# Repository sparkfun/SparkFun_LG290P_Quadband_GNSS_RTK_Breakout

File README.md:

SparkFun Quadband GNSS RTK Breakout - LG290P (Qwiic)
========================================

[*SparkFun Quadband GNSS RTK Breakout - LG290P (Qwiic) (GPS-26620)*](https://www.sparkfun.com/sparkfun-quadband-gnss-rtk-breakout-lg290p-qwiic.html)

The [SparkFun Quadband GNSS RTK Breakout - LG290P (Qwiic)](https://www.sparkfun.com/sparkfun-quadband-gnss-rtk-breakout-lg290p-qwiic.html) features the Quectel LG290P GNSS module. The board's dimensions, pin layout, and connectors are exactly the same as our very popular [SparkFun GPS-RTK-SMA Breakout - ZED-F9P (Qwiic)](https://www.sparkfun.com/sparkfun-gps-rtk-sma-breakout-zed-f9p-qwiic.html); and can be used as a drop-in replacement. The board also accommodates users with a diverse choice of interfaces including UART, SPI*, and I2C*.

The LG290P module is a quad-band, multi-constellation, high-precision, RTK GNSS receiver. The module is capable of simultaneously receiving signals from the `L1`, `L2`, `L5`, and `L6`/`E6` frequency bands of the GPS, GLONASS, Galileo, BDS, QZSS, and NavIC GNSS constellations. In addition, the module supports SBAS augmentation systems (WASS, EGNOS, BDSBAS, MSAS, GAGAN, and SDCM), PPP services* (BDS PPP-B2b, QZSS CLAS, MADOCA-PPP, and Galileo HAS), and RTK corrections for precision navigation with a fast convergence time and reliable performance.

The built-in NIC anti-jamming unit provides professional-grade interference signal detection and elimination algorithms, which effectively mitigate against multiple narrow-band interference sources and significantly improves the signal reception performance in complex electromagnetic environments. Additionally, the embedded algorithms ensure reliable positioning in complex scenarios such as urban environments and deep tree cover.

With its performance advantages of high-precision and low power consumption, this board is an ideal choice for high-precision navigation applications, such as intelligent robots, UAVs, precision agriculture, mining, surveying, and autonomous navigation.

> [!NOTE]
> `*`: Feature is still under development

> [!IMPORTANT]
> - Currently, only the UART interface is supported by the module. All three UART ports are broken out to the USB-C connector *(via CH342 USB-serial converter)*, 4-pin locking JST connector, and BlueSMiRF 6-pin header.
> - Additionally, the corrections for some of the PPP services may not be implemented yet.

Documentation
--------------

* **[Hookup Guide (mkdocs)](http://docs.sparkfun.com/SparkFun_LG290P_Quadband_GNSS_RTK_Breakout/)** - The hookup guide for the SparkFun Quadband GNSS RTK Breakout - LG290P (Qwiic) hosted by GitHub pages.<br>
   
* [SparkFun LG290P GNSS Arduino Library](https://github.com/sparkfun/SparkFun_LG290P_GNSS_Arduino_Library) - An Arduino library for the LG290P GNSS module

*Need to download or print our hookup guide?*

* [Print *(Print to PDF)* from Single-Page View](http://docs.sparkfun.com/SparkFun_LG290P_Quadband_GNSS_RTK_Breakout/print_view)

Repository Contents
-------------------

* **[/docs](/docs/)** - Online documentation files
    * [assets](/docs/assets/) - Assets files
        * [3d_model](/docs/assets/3d_model/) - Files for the 3D models
            * [3D CAD Model](/docs/assets/3d_model/cad_model.step) (.step)
        * [board_files](/docs/assets/board_files/) - Files for the product design
            * [KiCad Design Files](/docs/assets/board_files/kicad_files.zip) (.zip)
            * [Schematic](/docs/assets/board_files/schematic.pdf) (.pdf)
            * [Dimensions](/docs/assets/board_files/dimensions.pdf) (.pdf)
        * [component_documentation](/docs/assets/component_documentation/) - Datasheets for hardware components
        * [img/hookup_guide/](/docs/assets/img/hookup_guide/) - Images for hookup guide documentation
* **[/Hardware](/Hardware/)** - Hardware design files (.brd, .sch)
  * **[/Production](/Production/)** - Production files

Product Variants
----------------

- LG290P Variants
  - [GPS-26620](https://www.sparkfun.com/sparkfun-quadband-gnss-rtk-breakout-lg290p-qwiic.html) - v1.0, Initial Release
  - [GPS-26916](https://www.sparkfun.com/sparkfun-rtk-postcard.html) - SparkFun RTK Postcard *(w/ ESP32)*
- [GPS-28019](https://www.sparkfun.com/products/28019) - SparkFun Quadband GNSS RTK Breakout - LG580P (Qwiic)

Version History
---------------

* [v10](https://github.com/sparkfun/SparkFun_LG290P_Quadband_GNSS_RTK_Breakout/releases/tag/v10) - Initial Release

License Information
-------------------

This product is ***open source***!

Please review the [`LICENSE.md`](./LICENSE.md) file for license information.

If you have any questions or concerns about licensing, please contact technical support on our [SparkFun forums](https://community.sparkfun.com/).

Distributed as-is; no warranty is given.

- Your friends at SparkFun.

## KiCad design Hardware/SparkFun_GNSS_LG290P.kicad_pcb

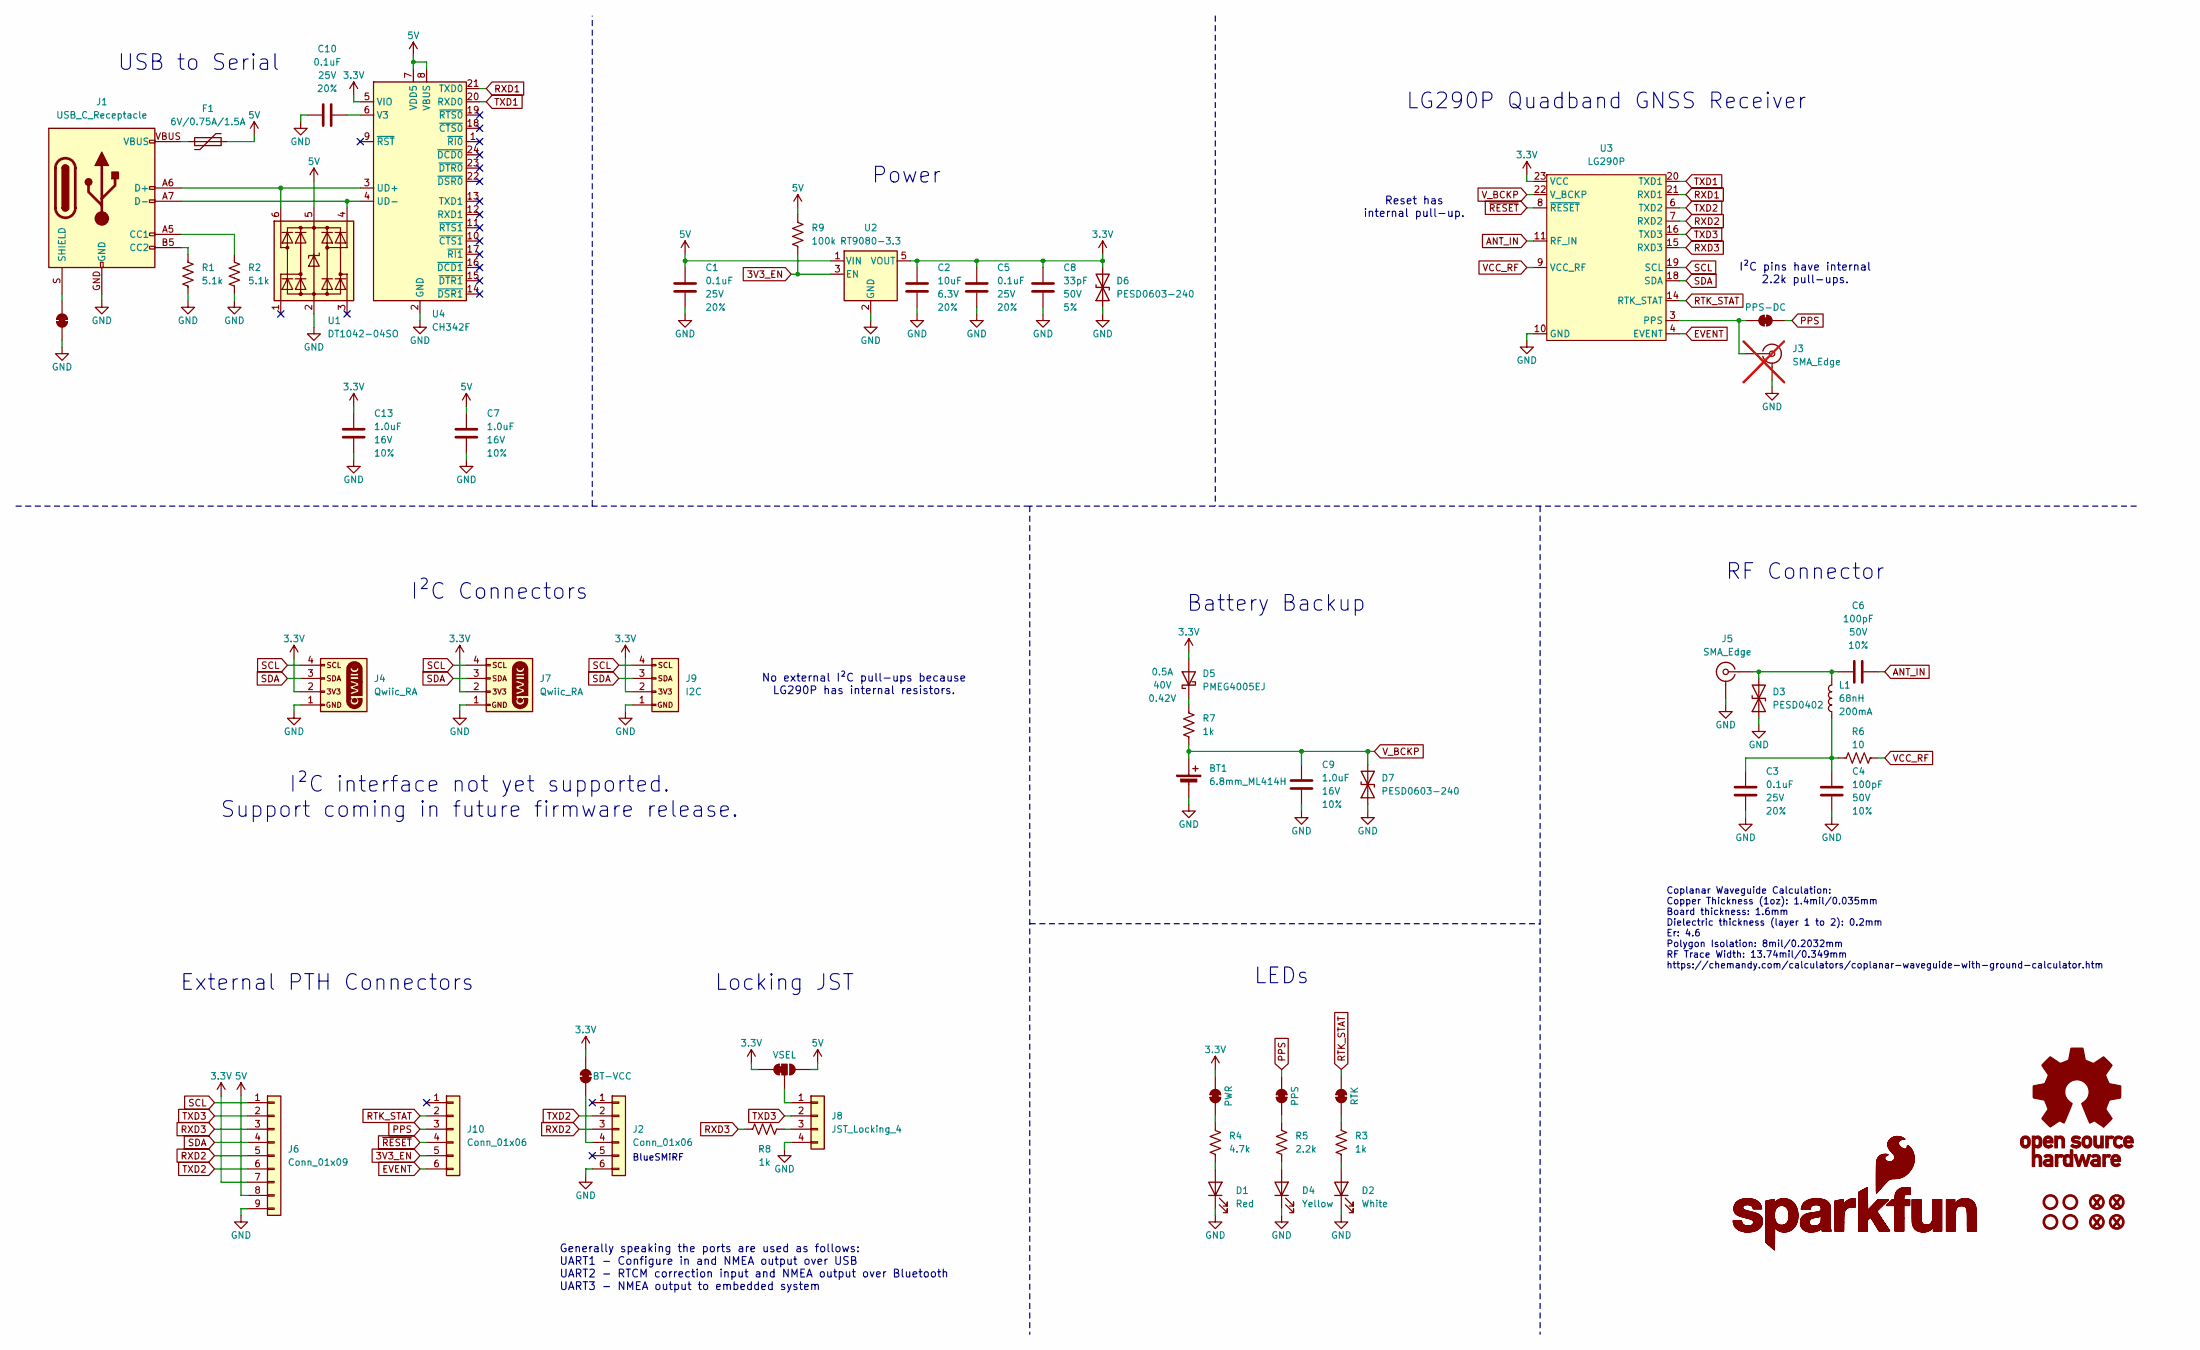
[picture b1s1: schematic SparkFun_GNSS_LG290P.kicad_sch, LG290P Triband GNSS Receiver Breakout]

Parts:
BT1: 6.8mm_ML414H; ML414H_IV01E
C1, C3, C5, C10: 0.1uF; C_0603_1608Metric; Voltage 25V; Tolerance 20%
C2: 10uF; C_0603_1608Metric; Voltage 6.3V; Tolerance 20%
C4: 100pF; C_0603_1608Metric; Voltage 50V; Tolerance 10%
C6: 100pF; C_0402_1005Metric; Voltage 50V; Tolerance 10%
C7, C9, C13: 1.0uF; C_0603_1608Metric; Voltage 16V; Tolerance 10%
C8: 33pF; C_0603_1608Metric; Voltage 50V; Tolerance 5%
D1: Red; LED_0603_1608Metric_Red
D2: White; LED_0603_1608Metric_White
D3: PESD0402; C_0402_1005Metric
D4: Yellow; LED_0603_1608Metric_Yellow
D5: PMEG4005EJ; SOD-323
D6, D7: PESD0603-240; C_0603_1608Metric
F1: 6V/0.75A/1.5A; 1206
FID1, FID2, FID3, FID4: Fiducial_0.5mm; Fiducial_0.5mm_Mask1mm
G1: OSHW_Logo; Creative_Commons_License
G3: SparkFun_Logo
G5: SparkFun_Logo; SparkFun_Logo_8mm
J1: USB_C_Receptacle; USB-C_16
J2, J10: Conn_01x06; 1x06
J3: SMA_Edge; not fitted
J4, J7: Qwiic_RA; JST_SMD_1.0mm-4_RA
J5: SMA_Edge
J6: Conn_01x09; 1x09
J8: JST_Locking_4; JST_SMD_1.25mm-4_Locking
J9: I2C; 1x04
JP1: BT-VCC; Jumper_2_NC_Trace
JP2: PWR; Jumper_2_NC_Trace
JP3: PPS; Jumper_2_NC_Trace
JP4: VSEL; Jumper_3_NC-1_Trace
JP5: RTK; Jumper_2_NC_Trace
JP6: PPS-DC; Jumper_2_NC_Trace
JP7: Jumper_2_NC_Trace
L1: 68nH; C_0402_1005Metric
R1, R2: 5.1k; R_0603_1608Metric
R3, R7, R8: 1k; R_0603_1608Metric
R4: 4.7k; R_0603_1608Metric
R5: 2.2k; R_0603_1608Metric
R6: 10; R_0603_1608Metric
R9: 100k; R_0603_1608Metric
ST1, ST2, ST3, ST4: Standoff
U1: DT1042-04SO; SOT23-6
U2: RT9080-3.3; SOT23-5
U3: LG290P; Quectel_LG290P
U4: CH342F; QFN-24-1EP_4x4mm_P0.5mm_EP2.7x2.7mm

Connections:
3.3V: C2.1, C5.1, C8.1, C13.1, D5.A, D6.2 (A2), J4.2, J6.7, J7.2, J9.2, JP1.2 (B), JP2.2 (B), JP4.1 (A), U2.5 (VOUT), U3.23 (VCC), U4.5 (VIO)
3V3_EN: J10.5, R9.2, U2.3 (EN)
5V: C1.1, C7.1, F1.2, J6.8, JP4.3 (B), R9.1, U1.5 (VCC), U2.1 (VIN), U4.7 (VDD5), U4.8 (VBUS)
ANT_IN: C6.2, U3.11 (RF_IN)
EVENT: J10.6, U3.4 (EVENT)
GND: BT1.-, C1.2, C2.2, C3.2, C4.2, C5.2, C7.2, C8.2, C9.2, C10.1, C13.2, D1.1 (K), D2.1 (K), D3.1 (A1), D4.1 (K), D6.1 (A1), D7.1 (A1), J1.GND, J2.6, J3.2 (Ext), J4.1, J5.2 (Ext), J6.9, J7.1, J8.4, J9.1, JP7.1 (A), R1.2, R2.2, U1.2 (GND), U2.2 (GND), U3.10 (GND), U3.12 (GND), U3.13 (GND), U3.24 (GND), U3.25 (GND), U4.2 (GND), U4.25 (GND)
unnamed: C3.1, C4.1, L1.1, R6.2
unnamed: D1.2 (A), R4.2
unnamed: D2.2 (A), R3.2
unnamed: C6.1, D3.2 (A2), J5.1 (In), L1.2
unnamed: D4.2 (A), R5.2
unnamed: D5.C, R7.1
unnamed: F1.1, J1.VBUS
unnamed: J1.A5 (CC1), R2.1
unnamed: J1.B5 (CC2), R1.1
unnamed: J1.S (SHIELD), JP7.2 (B)
unnamed: J2.4, JP1.1 (A)
unnamed: J3.1 (In), JP6.1 (A), U3.3 (PPS)
unnamed: J8.1, JP4.2 (C)
unnamed: J8.3, R8.2
unnamed: JP2.1 (A), R4.1
unnamed: JP3.1 (A), R5.1
unnamed: JP5.1 (A), R3.1
unnamed: J1.A7 (D-), J1.B7 (D-), U1.4 (I/O3), U4.4 (UD-)
unnamed: J1.A6 (D+), J1.B6 (D+), U1.6 (I/O4), U4.3 (UD+)
unnamed: C10.2, U4.6 (V3)
PPS: J10.3, JP3.2 (B), JP6.2 (B)
RTK_STAT: J10.2, JP5.2 (B), U3.14 (RTK_STAT)
RXD1: U3.21 (RXD1), U4.21 (TXD0)
RXD2: J2.3, J6.5, U3.7 (RXD2)
RXD3: J6.3, R8.1, U3.15 (RXD3)
SCL: J4.4, J6.1, J7.4, J9.4, U3.19 (SCL)
SDA: J4.3, J6.4, J7.3, J9.3, U3.18 (SDA)
TXD1: U3.20 (TXD1), U4.20 (RXD0)
TXD2: J2.2, J6.6, U3.6 (TXD2)
TXD3: J6.2, J8.2, U3.16 (TXD3)
VCC_RF: R6.1, U3.9 (VCC_RF)
V_BCKP: BT1.+, C9.1, D7.2 (A2), R7.2, U3.22 (V_BCKP)
~RESET: J10.4, U3.8 (~RESET)

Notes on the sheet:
I²C Connectors
Generally speaking the ports are used as follows: UART1 - Configure in and NMEA output over USB UART2 - RTCM correction input and NMEA output over Bluetooth UART3 - NMEA output to embedded system
Reset has internal pull-up.
I²C interface not yet supported. Support coming in future firmware release.
Coplanar Waveguide Calculation: Copper Thickness (1oz): 1.4mil/0.035mm Board thickness: 1.6mm Dielectric thickness (layer 1 to 2): 0.2mm Er: 4.6 Polygon Isolation: 8mil/0.2032mm RF Trace Width: 13.74mil/0.349mm https://chemandy.com/calculators/coplanar-waveguide-with-ground-calculator.htm
I²C pins have internal 2.2k pull-ups.
Locking JST
BlueSMiRF
Power
RF Connector
LEDs
LG290P Quadband GNSS Receiver
USB to Serial
Battery Backup
External PTH Connectors
No external I²C pull-ups because LG290P has internal resistors.

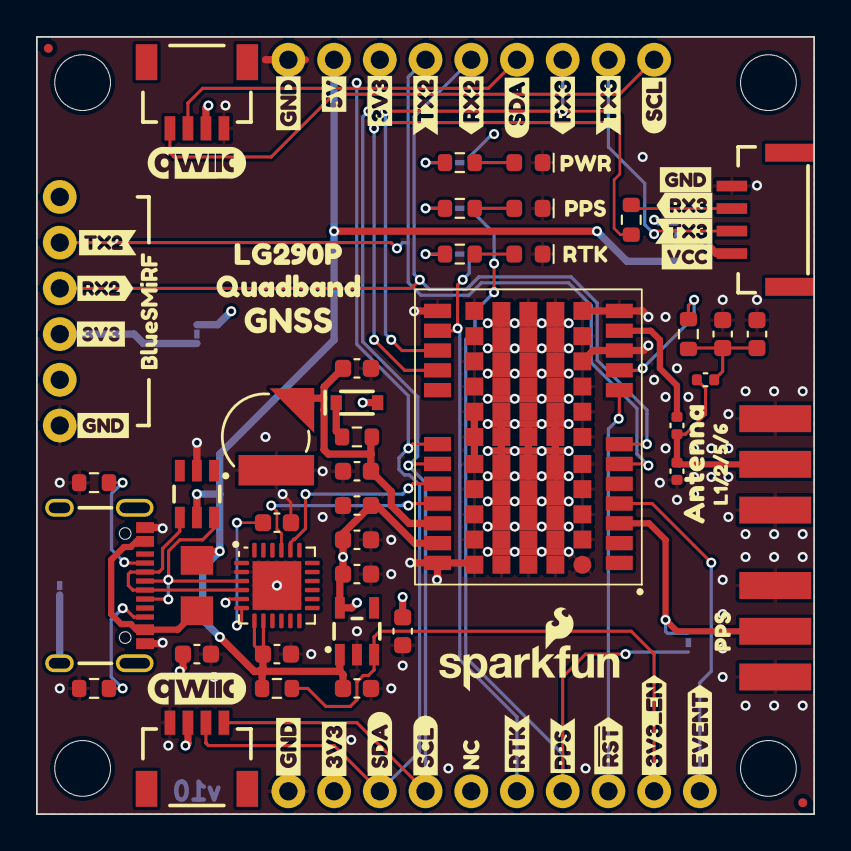
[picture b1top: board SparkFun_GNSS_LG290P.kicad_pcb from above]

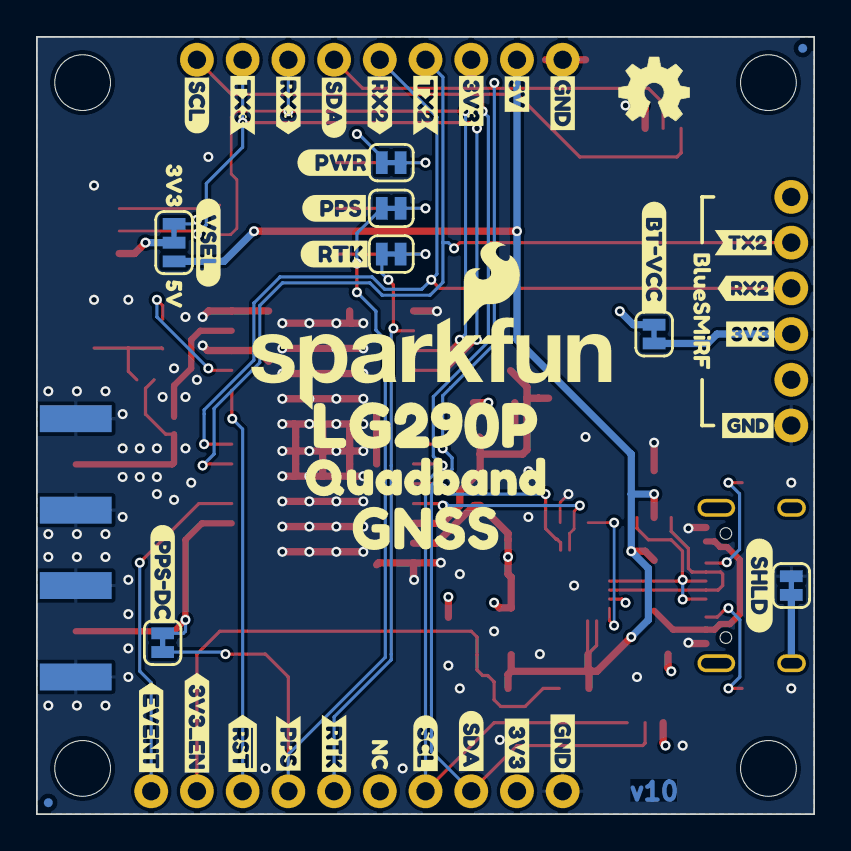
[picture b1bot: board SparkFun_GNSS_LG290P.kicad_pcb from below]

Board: 4 copper layers, 43.2 x 43.2 mm, 134 parts (46 on the bottom side), 39 nets.

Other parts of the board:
Ref**: Val**; OSHW_Logo_4mm
kibuzzard-64C2E6A3: G***; kibuzzard-64C2E6A3
kibuzzard-64C2E6BD: G***; kibuzzard-64C2E6BD
kibuzzard-64C2E6D6: G***; kibuzzard-64C2E6D6
kibuzzard-64C2E728: G***; kibuzzard-64C2E728
kibuzzard-64C2EB16: G***; kibuzzard-64C2EB16
kibuzzard-64C3DF93: G***; kibuzzard-64C3DF93
kibuzzard-64CB1646: G***; kibuzzard-64CB1646
kibuzzard-64CB1658: G***; kibuzzard-64CB1658
kibuzzard-64D296AE: G***; kibuzzard-64D296AE
kibuzzard-66C94FCB: G***; kibuzzard-66C94FCB
kibuzzard-66C9493A: G***; kibuzzard-66C9493A
kibuzzard-66C94934: G***; kibuzzard-66C94934
kibuzzard-66C94943: G***; kibuzzard-66C94943
kibuzzard-66CAA7B2: G***; kibuzzard-66CAA7B2
kibuzzard-66CAA7D2: G***; kibuzzard-66CAA7D2
kibuzzard-66CAA8C4: G***; kibuzzard-66CAA8C4
kibuzzard-66CAA8D1: G***; kibuzzard-66CAA8D1
kibuzzard-66CAA8D8: G***; kibuzzard-66CAA8D8
kibuzzard-66CAA8DF: G***; kibuzzard-66CAA8DF
kibuzzard-66CAA8E9: G***; kibuzzard-66CAA8E9
kibuzzard-66CAA8ED: G***; kibuzzard-66CAA8ED
kibuzzard-66CAA9A5, kibuzzard-66CAA9A5#2: G***; kibuzzard-66CAA9A5
kibuzzard-66CAA9AE, kibuzzard-66CAA9AE#2: G***; kibuzzard-66CAA9AE
kibuzzard-66CAA9CC: G***; kibuzzard-66CAA9CC
kibuzzard-66CAA9E1: G***; kibuzzard-66CAA9E1
kibuzzard-66CAA41A: G***; kibuzzard-66CAA41A
kibuzzard-66CAA70F: G***; kibuzzard-66CAA70F
kibuzzard-66CAA426, kibuzzard-66CAA426#2: G***; kibuzzard-66CAA426
kibuzzard-66CAA432, kibuzzard-66CAA432#2: G***; kibuzzard-66CAA432
kibuzzard-66CAA594: G***; kibuzzard-66CAA594
kibuzzard-66CAA834: G***; kibuzzard-66CAA834
kibuzzard-66CAAA3A: G***; kibuzzard-66CAAA3A
kibuzzard-66CAAA42: G***; kibuzzard-66CAAA42
kibuzzard-66CAAA64: G***; kibuzzard-66CAAA64
kibuzzard-66CB3A22: G***; kibuzzard-66CB3A22
kibuzzard-66CB3A29: G***; kibuzzard-66CB3A29
kibuzzard-66CB3AB2: G***; kibuzzard-66CB3AB2
kibuzzard-66CB3AEE: G***; kibuzzard-66CB3AEE
kibuzzard-66CB3B05: G***; kibuzzard-66CB3B05
kibuzzard-66CB3B6E: G***; kibuzzard-66CB3B6E
kibuzzard-66CB3B7A: G***; kibuzzard-66CB3B7A
kibuzzard-66CB3BAB: G***; kibuzzard-66CB3BAB
kibuzzard-66CB3BB4: G***; kibuzzard-66CB3BB4
kibuzzard-66CB3BBD: G***; kibuzzard-66CB3BBD
kibuzzard-66CB3BC8: G***; kibuzzard-66CB3BC8
kibuzzard-66CB3BD0: G***; kibuzzard-66CB3BD0
kibuzzard-66CB3BFF: G***; kibuzzard-66CB3BFF
kibuzzard-66CB3C6B: G***; kibuzzard-66CB3C6B
kibuzzard-66CB3C14: G***; kibuzzard-66CB3C14
kibuzzard-66CB3C73: G***; kibuzzard-66CB3C73
kibuzzard-66CB7E2C: G***; kibuzzard-66CB7E2C
kibuzzard-66CB37A9, kibuzzard-66CB37A9#2: G***; kibuzzard-66CB37A9
kibuzzard-66CB37CC: G***; kibuzzard-66CB37CC
kibuzzard-66CB37D7: G***; kibuzzard-66CB37D7
kibuzzard-66CB38B8: G***; kibuzzard-66CB38B8
kibuzzard-66CB38C4: G***; kibuzzard-66CB38C4
kibuzzard-66CB39E1, kibuzzard-66CB39E1#2: G***; kibuzzard-66CB39E1
kibuzzard-66CB82FB: G***; kibuzzard-66CB82FB
kibuzzard-66CB829C: G***; kibuzzard-66CB829C
kibuzzard-66CB830B: G***; kibuzzard-66CB830B
kibuzzard-66CB3887: G***; kibuzzard-66CB3887
kibuzzard-66CB3899: G***; kibuzzard-66CB3899
kibuzzard-66CB8004: G***; kibuzzard-66CB8004
kibuzzard-66CBD5AE: G***; kibuzzard-66CBD5AE
kibuzzard-6501FDDA, kibuzzard-6501FDDA#2: G***; kibuzzard-6501FDDA
kibuzzard-650880E6: G***; kibuzzard-650880E6

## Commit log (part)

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2024-08-28 Connect CH342 V3 to decoupling cap
2024-08-28 Reduce ground clearance to clear DRC error
2024-08-29 Add DRC exclusions
2024-09-23 Add TVS to 3V3 and VBATT. Add protocol spec.
2024-10-02 Make post design review changes. Add panel files.
2024-10-02 Initial docs setup
    Initial files to setup the hookup guide
2024-10-02 Move component documentation
    Move component documentation into the /docs directory for the hookup guide
2024-11-14 Moved the 3D model
    Moved the 3D model of the module into the /docs/assets/component_documentation directory
2024-11-14 Initial draft
    Initial draft for the hookup guide.
    Still reworking the information for the software configuration to setup RTK corrections.
2024-11-14 Update
    Change lists to `-`
    Update README for KiCad files
    Fix typos
2024-11-14 Video link and QR codes
    Update video link
    Add QR code for manufacturer video
    Update normal QR codes
2024-11-14 Build Docs
    Adds workflow for building documentation
2024-11-15 Update mkdocs.yml
    Update to recent changes
2024-11-15 Fix broken link
2024-11-15 Deployed d916cb2 with MkDocs version: 1.6.1
2024-12-20 Update Hookup Guide
2024-12-20 Deployed 0cf9bbf with MkDocs version: 1.6.1
2025-01-14 Add docs to support v04 firmware
2025-02-11 Deployed 3dfeb99 with MkDocs version: 1.6.1
2025-02-11 Update workflow
    Replace token variable
    Update cache action
    Add comments
2025-02-11 Deployed 324c4e9 with MkDocs version: 1.6.1
2025-04-04 add PyGPSClient LG290P configuration links
2025-05-21 Deployed 87c596e with MkDocs version: 1.6.1
2025-05-21 Update hardware_overview.md
    Fix product name to Quad-band
2025-05-21 Update component documentation
2025-05-21 Replace center tag
    Center tag is deprecated
    - Replaced w/ `<article style="text-align: center;" markdown>`
    - For video blocks `<article class="video-500px" style="text-align: center; margin: auto;" markdown>`
2025-05-21 Deployed be32b94 with MkDocs version: 1.6.1
2025-07-01 Remove authors plug-in
    Removes mkdocs-git-authors-plugin
2025-07-08 Update QGNSS versioning
    Revised from v2.0 to v2.x
    Link redirects to latest software
2025-07-09 Add firmware update
    Added a new section to the documentation detailing the firmware update process for the LG290P module, including references to the official manual and firmware sources. Included a warning about the sy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
2025-07-09 Update purchase link
    Adjusted the layout of the purchase button and QR code
2025-07-09 Deployed 4b4094e with MkDocs version: 1.6.1
2025-09-12 Update .gitignore
    Remove leftover merge conflict markers
    Consolidate duplicate entries
    Remove ignored file type
2025-09-12 Deployed 9075725 with MkDocs version: 1.6.1
2025-09-12 Update footprints
    Fixes file path, position, and orientation for the 3D models
2025-09-12 Update component documentation
    Updates the datasheet, manuals, application notes, etc. for the LG290P
2025-09-15 Deployed 3bc927b with MkDocs version: 1.6.1
2025-09-25 Update product URLs
    Updated for SEO compatibility
    Removed retired/discontinued products
2025-09-25 Add README.md
    Adds README file for the current directory
2025-09-25 Deployed 4e191d8 with MkDocs version: 1.6.1
2026-06-03 Deployed fd182da with MkDocs version: 1.6.1

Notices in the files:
parts and their libraries:
https://creativecommons.org/licenses/by-sa/4.0
Released under the Creative Commons Attribution Share-Alike 4.0 License
